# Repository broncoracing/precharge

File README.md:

# Precharge circuit
Precharge & voltage indicator circuit for BR23E

```bash
└── pcb
    ├── PCB layout
    ├── schematic
    └── etc
```

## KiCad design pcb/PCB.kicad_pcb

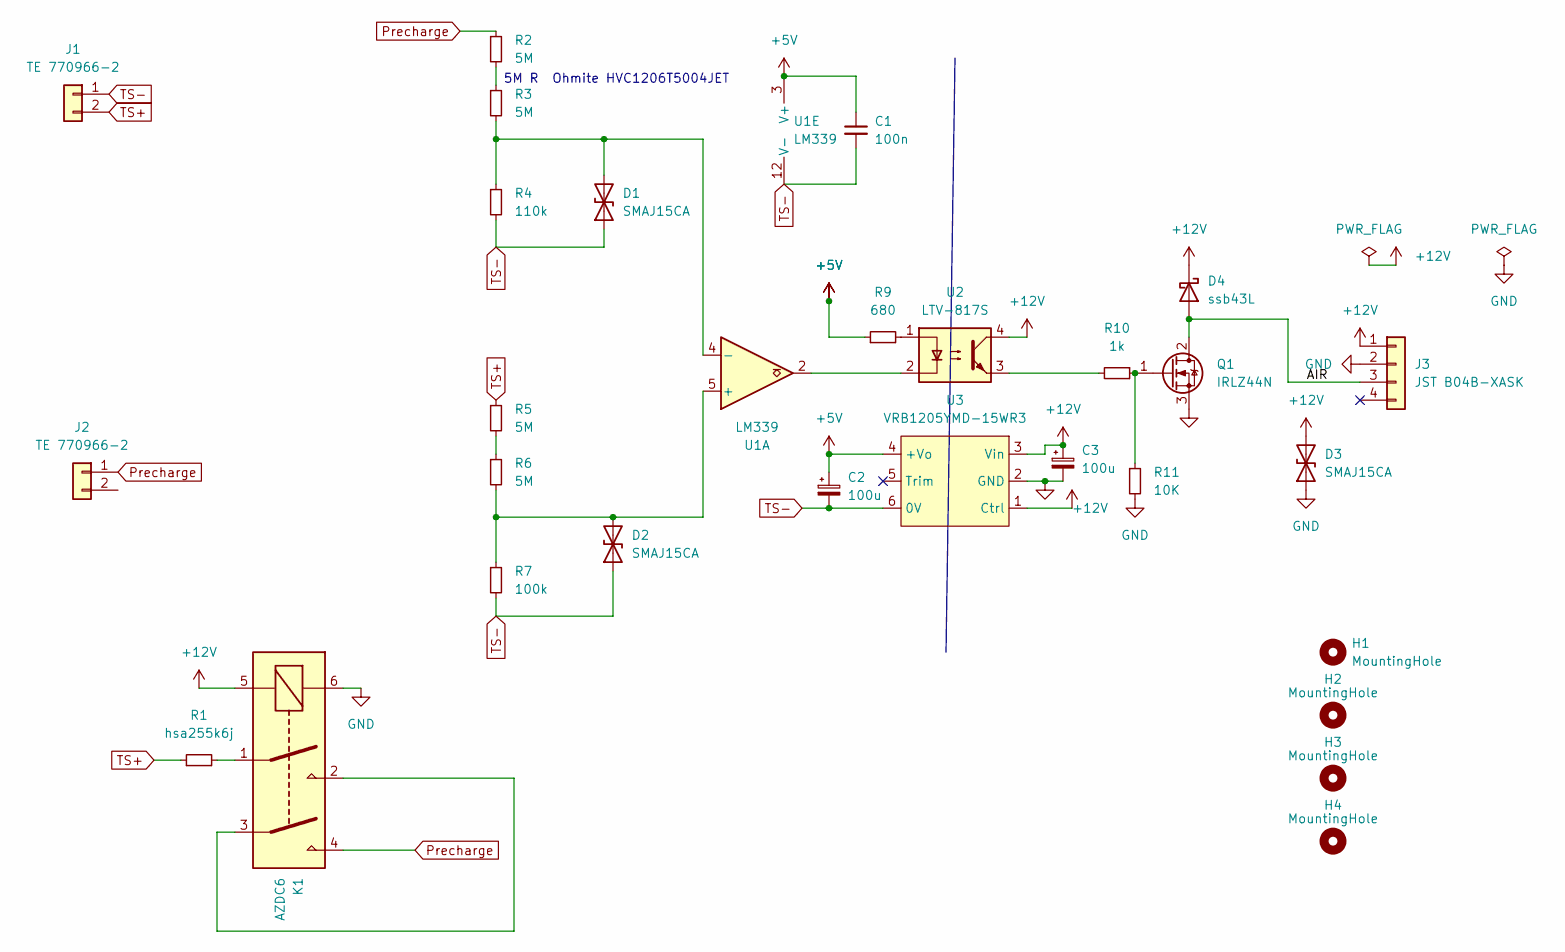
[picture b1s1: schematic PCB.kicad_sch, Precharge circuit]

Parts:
C1: 100n; C_0603_1608Metric
C2, C3: 100u; CP_Elec_6.3x7.7
D1, D2, D3: SMAJ15CA; D_SMA
D4: ssb43L; D_SMB
H1, H2, H3, H4: MountingHole; MountingHole_3.2mm_M3
J1, J2: TE 770966-2; TE_MATE-N-LOK_1-770966-x_1x02_P4.14mm_Horizontal
J3: JST B04B-XASK; JST_XA_B04B-XASK-1_1x04_P2.50mm_Vertical
K1: AZDC6
Q1: IRLZ44N; TO-263-3_TabPin2
R1: hsa255k6j
R2, R3, R5, R6: 5M; R_1206_3216Metric
R4: 110k; R_1206_3216Metric
R7: 100k; R_1206_3216Metric
R9: 680; R_0603_1608Metric
R10: 1k; R_0603_1608Metric
R11: 10K; R_0603_1608Metric
U1: LM339; TSSOP-14_4.4x5mm_P0.65mm
U2: LTV-817S; SMDIP-4_W9.53mm
U3: VRB1205YMD-15WR3

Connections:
+5V: C1.1, C2.1, R9.1, U1.3 (V+), U3.4 (+Vo)
+12V: C3.1, D3.2 (A2), D4.1 (K), J3.1, K1.5, U2.4, U3.1 (Ctrl), U3.3 (Vin)
/AIR: D4.2 (A), J3.3, Q1.2 (D)
GND: C3.2, D3.1 (A1), J3.2, K1.6, Q1.3 (S), R11.2, U3.2 (GND)
unnamed: D1.2 (A2), R3.2, R4.1, U1.4 (-)
unnamed: D2.2 (A2), R6.2, R7.1, U1.5 (+)
unnamed: K1.1, R1.2
unnamed: K1.2, K1.3
unnamed: Q1.1 (G), R10.1, R11.1
unnamed: R2.2, R3.1
unnamed: R5.2, R6.1
unnamed: R9.2, U2.1
unnamed: R10.2, U2.3
unnamed: U1.2, U2.2
Precharge: J2.1, K1.4, R2.1
TS+: J1.2, R1.1, R5.1
TS-: C1.2, C2.2, D1.1 (A1), D2.1 (A1), J1.1, R4.2, R7.2, U1.12 (V-), U3.6 (0V)

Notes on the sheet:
5M R Ohmite HVC1206T5004JET

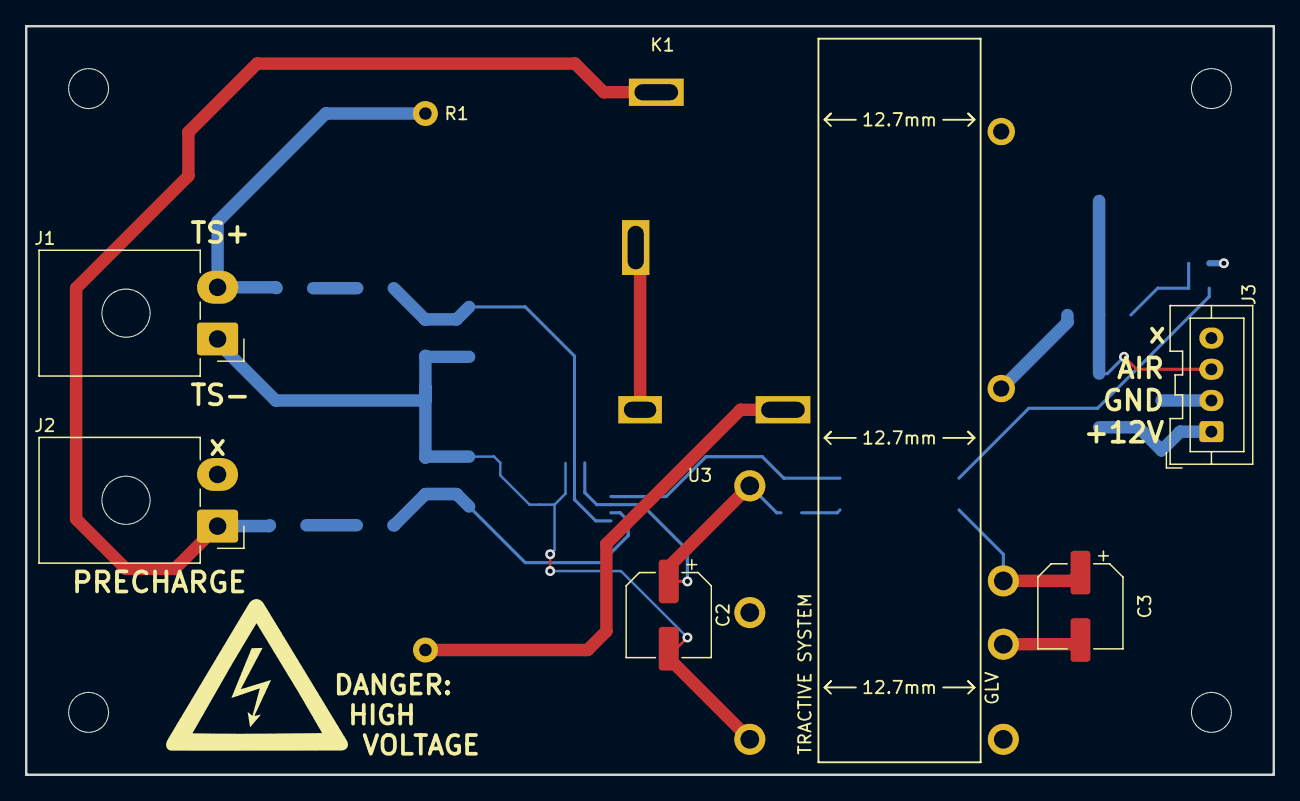
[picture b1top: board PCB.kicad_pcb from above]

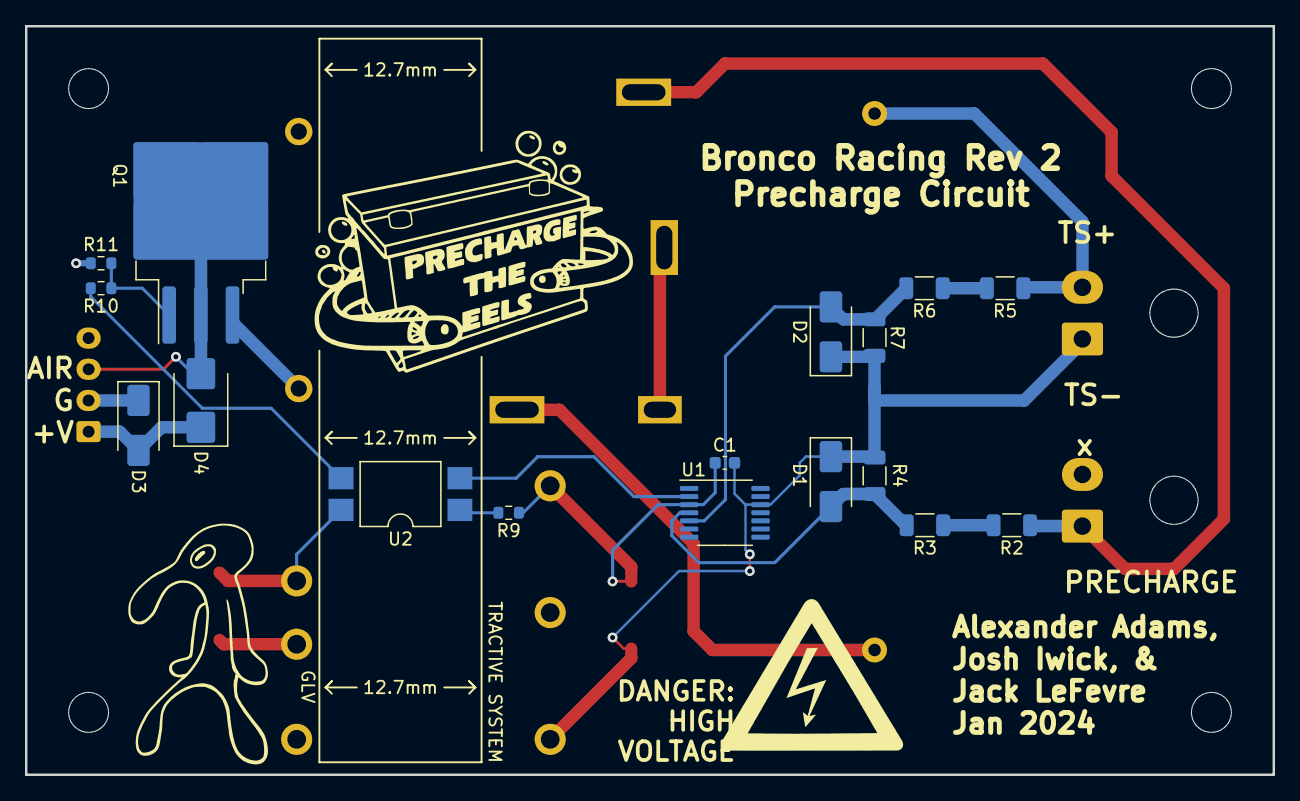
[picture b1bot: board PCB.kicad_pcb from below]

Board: 4 copper layers, 100.0 x 60.0 mm, 29 parts (17 on the bottom side), 17 nets.

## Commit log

2023-02-06 Precharge circuit start
2023-02-06 PC circuit sim
2023-02-22 Precharge PCB update
2023-02-26 Updated PCB Design
2023-03-01 pcb update precharge
2023-03-02 bbs home
2023-03-04 Added mounting holes and fixed drc violations
2023-03-07 Final? Pre/Dis
2023-11-20 Precharge W/o Discharge
2024-01-26 Re-layout pcb for br24
2024-03-13 fix backwards comparator
2024-04-07 update pcb too
